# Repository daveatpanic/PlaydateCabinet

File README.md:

# Playdate Cabinet
CAD and code for the Playdate Cabinet

	mirrorpi/ - Mirror port for the Raspberry Pi
	crank/ - KiCad files for crank sensor PCB, Arduino sketch for Seeeduino Xiao controller
	cabinet.skp - SketchUp CAD file for cabinet

Build the cabinet version with `make -C mirrorpi rpi`, or the physical-Playdate-controller version with `make -C mirrorpi rpi-no-controls`. The latter accepts `--viewport=x,y,width,height` for an optional destination rectangle, for example:

	./mirrorpi/mirror-no-controls --viewport=40,48,640,384

BOM

	Display: Scepter ‎E205W-16003R 20" 1600x900 75Hz Ultra Thin LED Monitor
	Raspberry Pi 3 B+
	EG STARTS JXGF-5Pin-Stick Arcade Joystick
	3x Reyann Black Happ Type Standard Arcade Push Button with Microswitch

Paint: Rustoleum Painter's Touch 2x Golden Sunset

raspi-config: enable serial, but not login over serial

add `dwc_otg.speed=1 video=HDMI-A-1:1280x720M@60` to cmdline.txt

add

	hdmi_group=1
	hdmi_drive=2

to [all] in config.txt, create /etc/asound.conf:

	defaults.pcm.card 1
	defaults.ctl.card 1

do crontab -e, add

	@reboot /home/pi/runmirror.sh

_Playdate Cabinet is a side project, not a Panic product! Please email dave@panic.com with questions, not Playdate support!_

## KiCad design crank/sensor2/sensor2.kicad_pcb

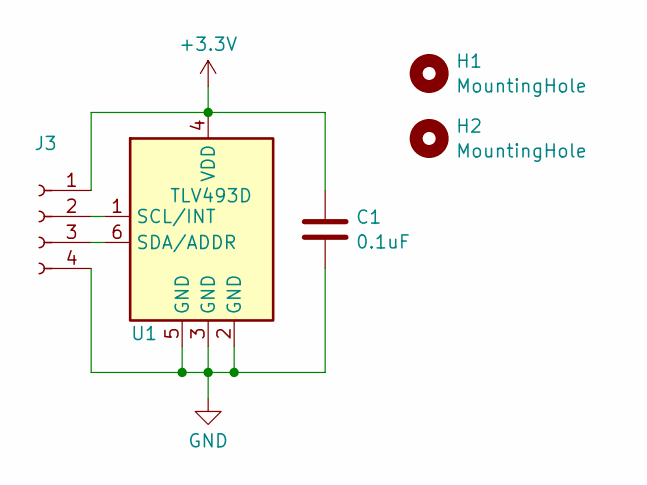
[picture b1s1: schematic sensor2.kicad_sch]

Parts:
C1: 0.1uF; C_0603_1608Metric
H1, H2: MountingHole; MountingHole_2mm
J3: Conn_01x04_Socket; PinSocket_1x04_P2.54mm_Vertical
U1: TLV493D; SOT-23-6

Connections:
+3.3V: C1.1, J3.1, U1.4 (VDD)
GND: C1.2, J3.4, U1.2 (GND), U1.3 (GND), U1.5 (GND)
unnamed: J3.2, U1.1 (SCL/INT)
unnamed: J3.3, U1.6 (SDA/ADDR)

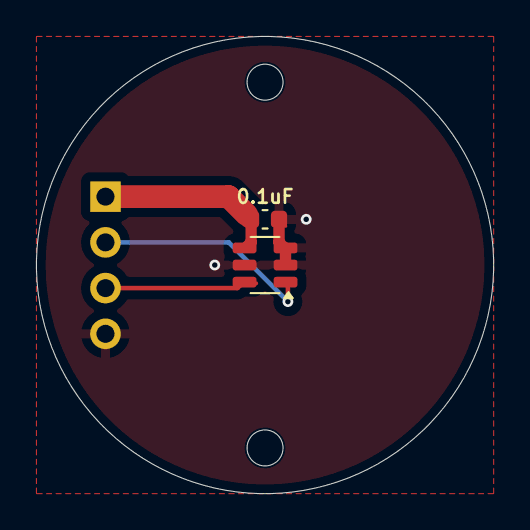
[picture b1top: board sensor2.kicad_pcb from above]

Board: 2 copper layers, 25.4 x 25.4 mm, 5 parts (1 on the bottom side), 4 nets.

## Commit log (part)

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2025-01-02 test commit
2025-03-22 added .gitignore
2025-03-22 added include check
2025-03-22 oh right, this is a header
2025-03-22 fuuuuuuuuuuuh
2025-03-22 moar files!!
2025-03-22 added image
2025-03-22 added BOM, sorta
2025-03-23 added launch accessories
2025-03-28 taking crank in and out sends "dockcrank" command
2025-03-28 check isdigit(readbuf[0]), not b
2025-03-28 reset readpos after \n
2025-03-30 swapped crank ic power pins
2025-03-30 removed dumb switch, forgot that I could just power the second sensor directly from gpio
2025-03-30 cleanup
2025-03-30 added kicad backup folders
2025-03-30 added notes about setting up audio, autoboot
2025-03-30 added pinout
2025-03-30 fixed pin mismatch
2025-03-30 mirrorjr -> mirrorpi
2025-03-30 colorized version of the 3d demo from the playdate sdk, using mirror's color mode
2025-03-31 wait for A button to be pressed before going into mirror loop
